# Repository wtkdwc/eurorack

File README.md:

# eurorack  
repo for eurorack creations  

s2m - simple passive stereo to mono converter

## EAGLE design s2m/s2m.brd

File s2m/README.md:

# s2m   
simple stereo to dual mono splitter x2 in 4hp

cc-by-sa

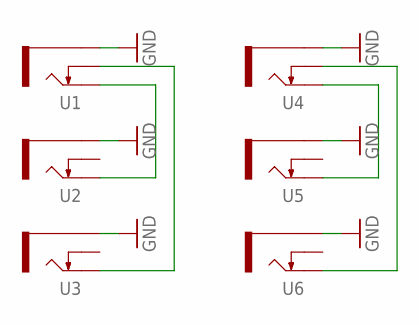
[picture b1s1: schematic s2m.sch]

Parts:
U1, U2, U3, U4, U5, U6: THONKICONNNEW; WQP-PJ301M-12_JACK

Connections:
GND: U1.P$3_SLEEVE (SLEEVE), U2.P$3_SLEEVE (SLEEVE), U3.P$3_SLEEVE (SLEEVE), U4.P$3_SLEEVE (SLEEVE), U5.P$3_SLEEVE (SLEEVE), U6.P$3_SLEEVE (SLEEVE)
unnamed: U1.P$2_SWITCH (SWITCH), U3.P$1_TIP (TIP)
unnamed: U1.P$1_TIP (TIP), U2.P$1_TIP (TIP)
unnamed: U4.P$2_SWITCH (SWITCH), U6.P$1_TIP (TIP)
unnamed: U4.P$1_TIP (TIP), U5.P$1_TIP (TIP)

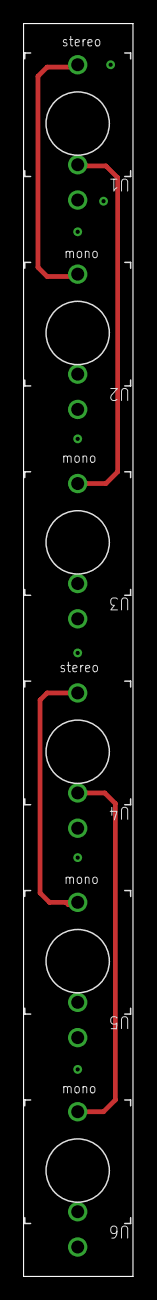
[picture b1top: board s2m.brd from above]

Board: 2 copper layers, 9.3 x 106.5 mm, 6 parts (0 on the bottom side), 5 nets.

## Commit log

2021-01-21 s2m init commit
2024-11-09 drum editor html

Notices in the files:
s2m/s2m.brd:
cc-by-sa wtk.dwc
